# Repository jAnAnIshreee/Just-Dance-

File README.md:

# Just-Dance-
A from-scratch reimagining of the Wii game "Just Dance": custom motion controller hardware (TM4C ARM Cortex-M4, SPI IMU, DAC audio) running on-device ML for real-time dance recognition, with MQTT syncing multiple controllers over Wi-Fi. Group project.
 # TinyML Embedded Gesture Classifier

I built this project with a team of individuals as a real-time embedded gesture-recognition system with a custom PCB using TM4C123 microcontrollers, LSM6DSOX IMUs, ESP8266 wireless communication, and fixed-point TinyML inference.

<p align="center">
  <em>Custom PCB and handheld controller modules used in the embedded gesture classification system</em>
</p>

The system captures motion from handheld controller modules, segments raw IMU data into meaningful gesture windows, extracts engineered features, runs lightweight classifiers directly on-device, and streams results to a central hub and host display. The full pipeline runs on embedded hardware rather than relying on a PC for inference.

---

## Overview

My goal with this project was to design a complete embedded system capable of classifying human motion under tight hardware constraints.

Each controller:

* samples a 6-axis IMU in real time
* performs filtering and calibration
* segments motion into gesture windows
* extracts a compact feature vector
* classifies gestures using rule-based logic and TinyML models

A central hub coordinates timing, aggregates controller outputs over ESP8266, and forwards results to a PC over UART for visualization.

---

## Key Features

* Real-time gesture classification on TM4C123 microcontrollers
* LSM6DSOX accelerometer/gyroscope integration over I2C
* Deterministic scheduling using a free-running hardware timer
* Fixed 5-second calibration stage for bias stabilization
* Tunable motion segmentation engine
* 32-feature embedded feature extraction pipeline
* Fixed-point TinyML inference (no floating point at runtime)
* Hybrid detection: neural networks + rule-based scoring
* ESP8266 wireless communication between modules
* UART protocol for structured output (`SEG` and `DETECT`)
* EEPROM-backed configuration persistence
* Multi-module embedded architecture (controllers + hub + host)

---

## System Architecture

```text
Controller Modules (TM4C + IMU)
    ↓
Sensor processing + segmentation
    ↓
Feature extraction (32 features)
    ↓
TinyML / rule-based classification
    ↓
ESP8266 wireless messages
    ↓
Central Hub (TM4C)
    ↓
UART output
    ↓
Host PC (Python visualization/logging)
```

A key design decision I made was to keep all classification on the embedded controllers. The PC is only used for visualization and logging, not inference.

---

## Repository Structure

```text
sw/
  sw_Player1_Controller/   → Controller firmware
  sw_Player2_Controller/   → Second controller firmware
  sw_Audio/                → Central hub firmware
  sw_Display/              → Python host interface

hw/                        → KiCad hardware design files
Resources/                 → Datasheets and references
```

### Main Entry Points

* `sw_Player1_Controller/src/Lab1.c`
* `sw_Player2_Controller/sw/src/Lab1.c`
* `sw_Audio/sw/src_latest/Lab5.c`

---

## Embedded Gesture Pipeline

Each controller runs a full embedded ML pipeline:

```text
IMU read
→ axis remap
→ filtering
→ calibration
→ segmentation
→ feature extraction
→ classification
→ output
```

### IMU Processing

I read accelerometer and gyroscope data over I2C and remap axes into a consistent real-world coordinate system:

```text
IRL X = sensor Y  
IRL Y = sensor Z  
IRL Z = sensor X  
```

---

### Calibration

At startup, I run a strict 5000 ms calibration phase using timer-based scheduling. This avoids drift and ensures stable baseline values for bias and gravity compensation.

---

### Real-Time Scheduling

I use Timer0A as a free-running hardware timer and schedule all sampling relative to time instead of loop delays. This keeps behavior deterministic even with UART output or I2C latency.

---

### Motion Segmentation

I designed a segmentation engine that detects meaningful motion using:

* energy thresholds
* quiet-window detection
* min/max segment sizes
* cooldown timing

Each gesture can override segmentation parameters, which makes the system flexible across very different motion types.

---

## Feature Extraction

For each segment, I compute 32 engineered features describing motion shape and intensity.

Examples include:

* duration and sample count
* vertical displacement and total travel
* cross-body movement
* oscillation and slope changes
* total acceleration and gyro energy
* peak timing and normalized feature ratios
* spin characteristics
* energy per sample

Instead of feeding raw time-series data into a large model, I compress each gesture into a compact feature vector to stay within embedded constraints.

---

## TinyML Inference

I implemented small neural networks directly in firmware using fixed-point math.

Typical structure:

```text
16 inputs → 3 hidden (ReLU) → 1 output
```

All weights, biases, and normalization parameters are stored as scaled integers. This avoids floating-point overhead and keeps inference fast and deterministic.

Some gestures use ML models, while others use rule-based scoring depending on how well they can be defined analytically.

---

## Output Protocol

The system outputs structured UART messages:

### Feature Data

```text
SEG,<MOVE>,<32 values>
```

### Final Detection

```text
DETECT,<MOVE>,<score>
```

I use `SEG` for debugging/training and `DETECT` as the final classification output.

---

## Cumulative Scoring

Instead of classifying every segment independently, I accumulate scores across a gesture window and only output a final detection after enough evidence is collected.

This significantly reduces noise and false positives.

---

## Central Hub

The hub is another TM4C system that:

* synchronizes controller start timing
* receives wireless data from controllers
* forwards results over UART
* manages timing-sensitive coordination

---

## Host Interface

I wrote a Python interface using:

* `pyserial` for communication
* `tkinter` for UI
* `opencv` / `Pillow` for visualization

This layer is purely for monitoring—the embedded system performs all classification.

---

## Hardware

This system is built on:

* TM4C123 microcontrollers
* LSM6DSOX IMUs
* ESP8266 modules
* DAC/audio hardware (hub side)
* custom KiCad-designed boards

All hardware files are included in the `hw/` directory.

---

## Why This Project Matters

This project combines:

* real-time embedded systems
* IMU signal processing
* motion segmentation
* feature engineering
* TinyML on constrained hardware
* wireless embedded communication

The most important aspect is that the entire ML pipeline runs **on-device**, making it a true embedded TinyML system rather than a PC-based demo.

---

## Future Improvements

* Modularize controller firmware
* Formalize ML training/export pipeline
* Add evaluation metrics (accuracy, confusion matrix)
* Improve host visualization tools
* Add hardware/system diagrams

---

## Status

This is a working embedded system prototype with real-time gesture classification, multi-device coordination, and on-device ML inference. The core pipeline is fully implemented and functional on embedded hardware.

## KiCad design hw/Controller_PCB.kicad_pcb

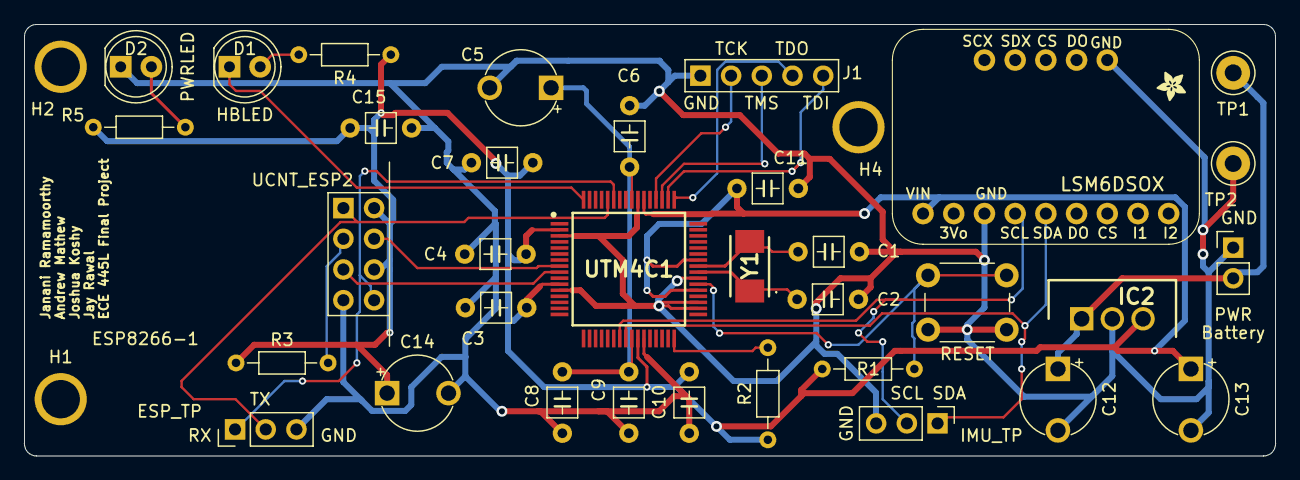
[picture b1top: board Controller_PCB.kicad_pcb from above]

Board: 2 copper layers, 103.5 x 35.7 mm, 39 parts (0 on the bottom side), 22 nets.

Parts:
C1, C2: 10pF C0G; C_Axial_200mil
C3, C6, C7, C9: 0.1uF; C_Axial_200mil
C4, C10: 0.01uF; C_Axial_200mil
C5: 2.2uF; CP_Radial_Tantal200mil
C8, C11: 1uF; C_Axial_200mil
C12, C13: 4.7uF; CP_Radial_Tantal200mil
C14: 4.7 uf; CP_Radial_Tantal200mil
C15: 0.1 uf; C_Axial_200mil
D1: HBLED; LED_D5.0mm
D2: PWRLED; LED_D5.0mm
H1, H2, H4: MountingHole_4_40
IC2: LM2937ET-3.3_NOPB; TO254P470X1028X1955-3P
IMU_TP: Conn_01x03; PinHeader_1x03_P2.54mm_Vertical
J1: JTAG; PinHeader_1x05_P2.54mm_Vertical
J2: Battery; PinHeader_1x02_P2.54mm_Vertical
J3: Conn_01x03; PinHeader_1x03_P2.54mm_Vertical
JP1: 1X09_ROUND_70
JP2: 1X05_ROUND_70
R1, R3: 10k; R_Axial_DIN0204_L3.6mm_D1.6mm_P7.62mm_Horizontal
R2: 1M; R_Axial_DIN0204_L3.6mm_D1.6mm_P7.62mm_Horizontal
R4, R5: 220; R_Axial_DIN0204_L3.6mm_D1.6mm_P7.62mm_Horizontal
RESET: Reset; SW_PUSH_6mm
TP1: TP_BAT; TestPoint_Loop_D3.50mm_Drill1.4mm_Beaded
TP2: TP_GND; TestPoint_Loop_D3.50mm_Drill1.4mm_Beaded
U$9: ADAFRUIT_2.5MM
UCNT_ESP2: ESP8266-1; ESP8266_FemaleConnector
UTM4C1: TM4C123GH6PMIR; QFP50P1200X1200X160-64N
Y1: ABM3-16.000MHZ-B2-T; ABM3

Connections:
3V3CNT: C3.1, C4.1, C7.1, C10.1, C11.1, C13.1, C14.1, C15.1, IC2.3 (OUTPUT), JP1.1, R1.1, R2.1, R3.1, R4.1, R5.1, UCNT_ESP2.6 (Ch_PD), UCNT_ESP2.8 (Vcc), UTM4C1.2 (VDDA), UTM4C1.11 (VDD_1), UTM4C1.26 (VDD_2), UTM4C1.37 (VBAT), UTM4C1.42 (VDD_3), UTM4C1.54 (VDD_4)
/Lab7_microcontroller/LDO: C5.1, C6.1, C8.1, C9.1, UTM4C1.25 (VDDC_1), UTM4C1.56 (VDDC_2)
/Lab7_microcontroller/OSC1: C1.1, UTM4C1.41 (OSC1), Y1.2
/Lab7_microcontroller/OSC2: C2.1, UTM4C1.40 (OSC0), Y1.1
/Lab7_microcontroller/Reset: R1.2, RESET.2, UTM4C1.38 (~RST)
/Lab7_microcontroller/TCK: J1.2 (B), UTM4C1.52 (PC0/TCK/SWCLK)
/Lab7_microcontroller/TDI: J1.5 (C), UTM4C1.50 (PC2/TDI)
/Lab7_microcontroller/TDO: J1.4 (C), UTM4C1.49 (PC3/TDO/SWO)
/Lab7_microcontroller/TMS: J1.3 (C), UTM4C1.51 (PC1/TMS/SWDIO)
GND: C1.2, C2.2, C3.2, C4.2, C5.2, C6.2, C7.2, C8.2, C9.2, C10.2, C11.2, C12.2, C13.2, C14.2, C15.2, D2.1 (K), IC2.2 (GND), IMU_TP.3, J1.1 (A), J2.1 (A), J3.3, JP1.3, JP2.1, RESET.1, TP2.1, UCNT_ESP2.4 (GND), UTM4C1.3 (GNDA), UTM4C1.12 (GND_1), UTM4C1.27 (GND_2), UTM4C1.34 (XOSC0), UTM4C1.35 (GNDX), UTM4C1.39 (GND_3), UTM4C1.55 (GND_4)
unnamed: D1.2 (A), R4.2
unnamed: D2.2 (A), R5.2
unnamed: R3.2, UCNT_ESP2.2 (GPIO0)
unnamed: R2.2, UTM4C1.32 (~WAKE)
PA6: IMU_TP.2, JP1.4, UTM4C1.23 (PA6)
PA7: IMU_TP.1, JP1.5, UTM4C1.24 (PA7)
PD3: D1.1 (K), UTM4C1.64 (PD3)
PE0: UCNT_ESP2.3 (GPIO2), UTM4C1.9 (PE0)
PE1: UCNT_ESP2.7 (Reset), UTM4C1.8 (PE1)
PE4: J3.1, UCNT_ESP2.5 (TxD), UTM4C1.59 (PE4)
PE5: J3.2, UCNT_ESP2.1 (RxD), UTM4C1.60 (PE5)
V_BAT: C12.1, IC2.1 (INPUT), J2.2 (B), TP1.1
